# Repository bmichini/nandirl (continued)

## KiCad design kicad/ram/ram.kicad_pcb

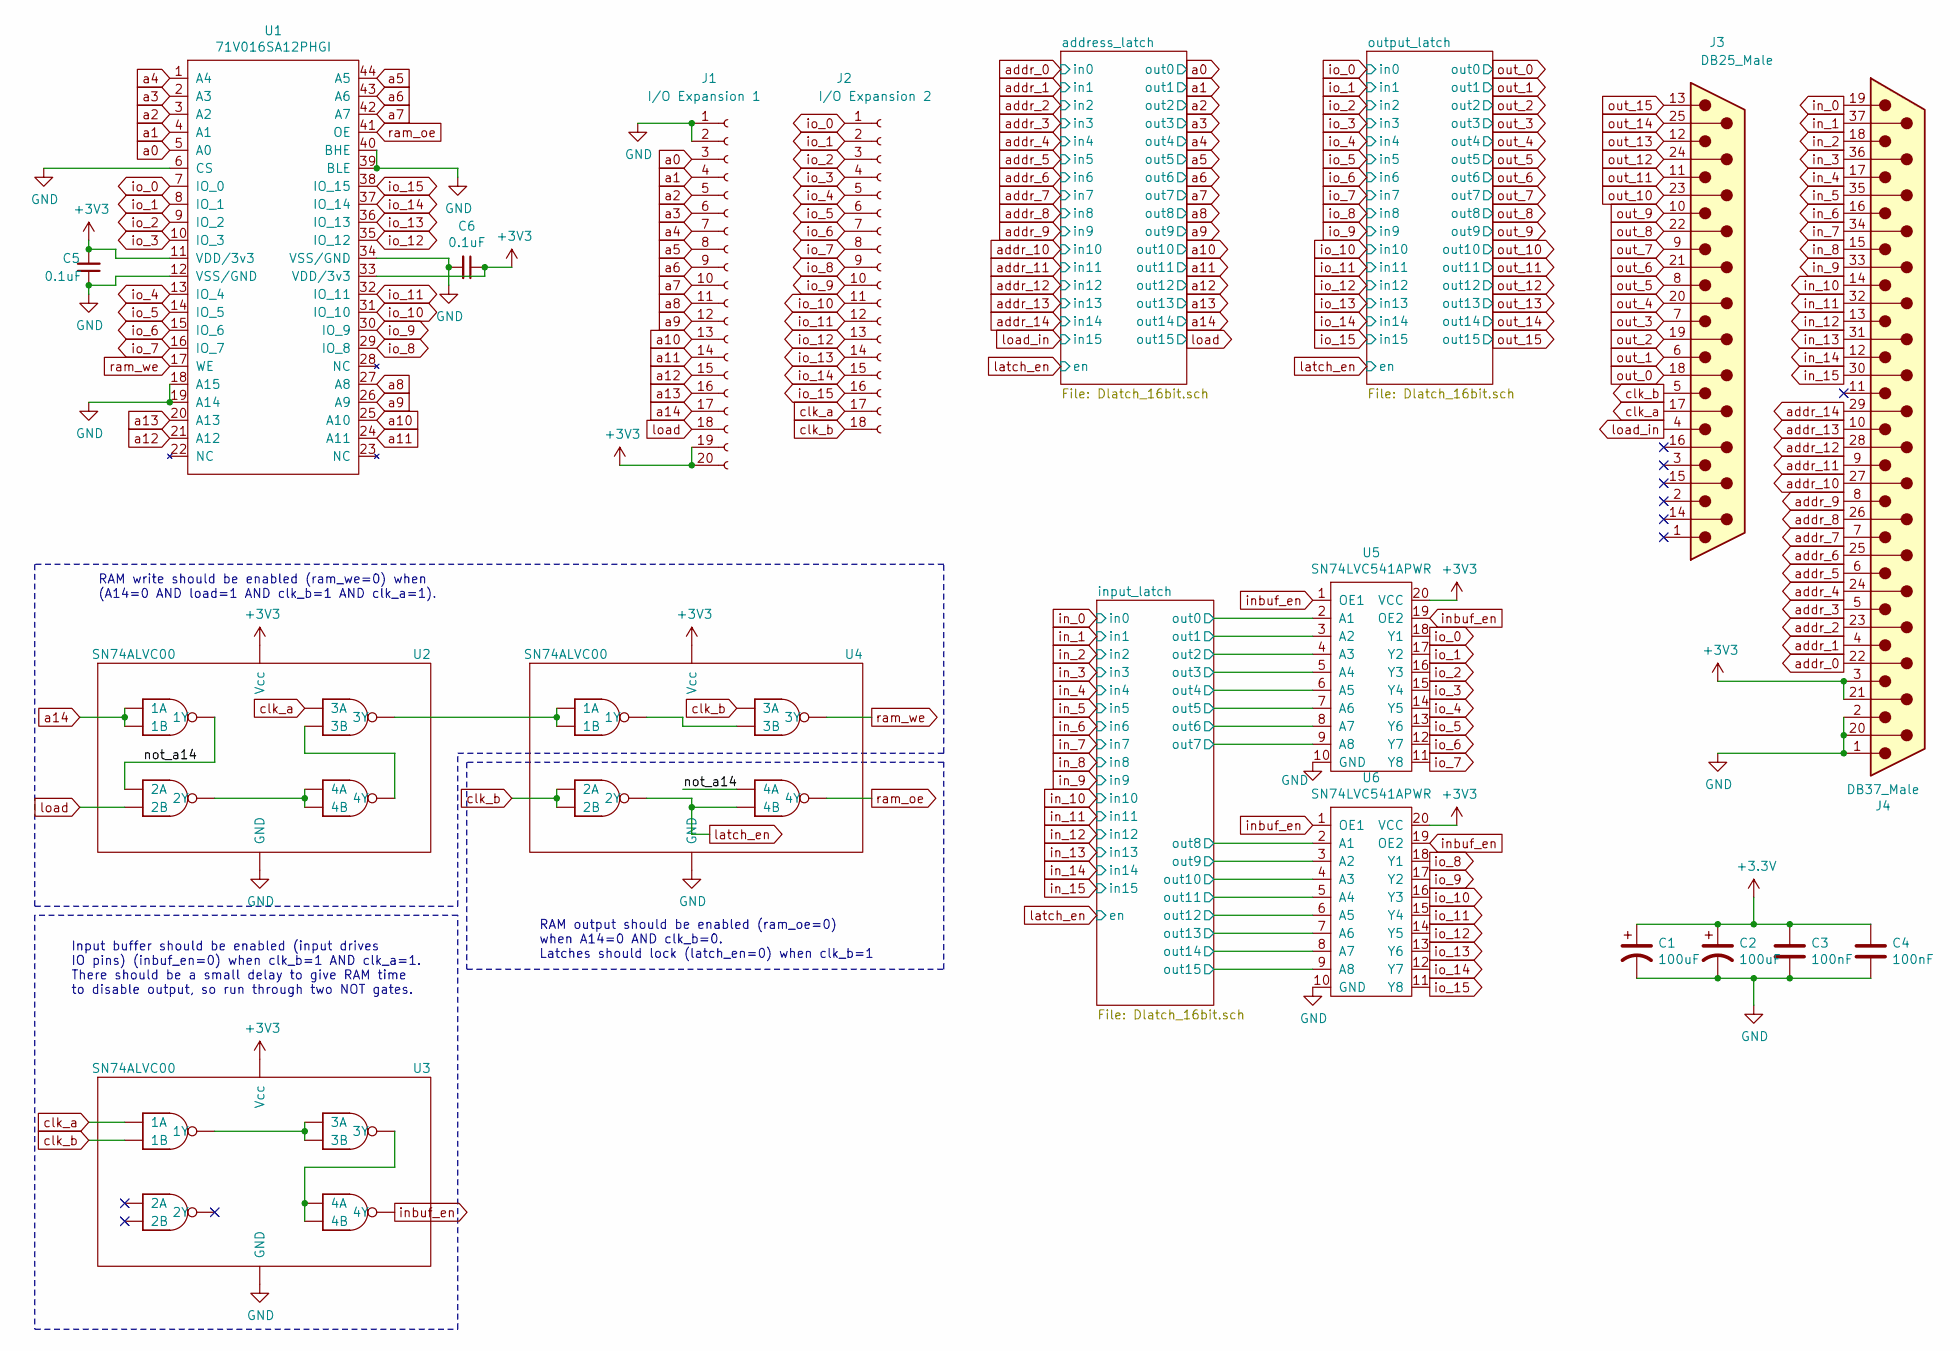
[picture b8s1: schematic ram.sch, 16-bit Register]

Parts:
C1, C2: 100uF; CP_Radial_D8.0mm_P2.50mm; Digikey PN P15797CT-ND
C3, C4: 100nF; C_Disc_D5.0mm_W2.5mm_P5.00mm; Digikey PN BC5229CT-ND
C5, C6: 0.1uF; C_1206_3216Metric; Digikey PN 399-C1206C104K5RAC7800CT-ND
J1: I/O Expansion 1; PinHeader_2x10_P2.54mm_Vertical
J2: I/O Expansion 2; PinHeader_2x09_P2.54mm_Vertical
J3: DB25_Male; DSUB-25_Male_Horizontal_P2.77x2.84mm_EdgePinOffset7.70mm_Ho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; Digikey PN AE10980-ND
J4: DB37_Male; DSUB-37_Male_Horizontal_P2.77x2.84mm_EdgePinOffset7.70mm_Ho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; Digikey PN AE10986-ND
U1: 71V016SA12PHGI; TSOP-II-44_10.16x18.41mm_P0.8mm; Digikey PN 800-2609-5-ND
U2, U3, U4: SN74ALVC00; TSSOP-14_4.4x5mm_P0.65mm; Digikey PN 296-5104-1-ND
U5, U6: SN74LVC541APWR; TSSOP-20_4.4x6.5mm_P0.65mm; Digikey PN 296-8521-1-ND

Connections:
/input_latch/out0: U5.2 (A1); also elsewhere on the board
/input_latch/out1: U5.3 (A2); also elsewhere on the board
/input_latch/out2: U5.4 (A3); also elsewhere on the board
/input_latch/out3: U5.5 (A4); also elsewhere on the board
/input_latch/out4: U5.6 (A5); also elsewhere on the board
/input_latch/out5: U5.7 (A6); also elsewhere on the board
/input_latch/out6: U5.8 (A7); also elsewhere on the board
/input_latch/out7: U5.9 (A8); also elsewhere on the board
/input_latch/out8: U6.2 (A1); also elsewhere on the board
/input_latch/out9: U6.3 (A2); also elsewhere on the board
/input_latch/out10: U6.4 (A3); also elsewhere on the board
/input_latch/out11: U6.5 (A4); also elsewhere on the board
/input_latch/out12: U6.6 (A5); also elsewhere on the board
/input_latch/out13: U6.7 (A6); also elsewhere on the board
/input_latch/out14: U6.8 (A7); also elsewhere on the board
/input_latch/out15: U6.9 (A8); also elsewhere on the board
/not_a14: U2.3 (1Y), U2.4 (2A), U4.12 (4A)
GND: C1.2, C2.2, C3.2, C4.2, C5.1, C6.2, J1.1, J1.2, J4.1, J4.2, J4.20, U1.6 (CS), U1.12 (VSS/GND), U1.18 (A15), U1.19 (A14), U1.34 (VSS/GND), U1.39 (BLE), U1.40 (BHE), U2.7 (GND), U3.7 (GND), U4.7 (GND), U5.10 (GND), U6.10 (GND); also elsewhere on the board
unnamed: U2.8 (3Y), U4.1 (1A), U4.2 (1B)
unnamed: U2.10 (3B), U2.11 (4Y)
unnamed: U2.6 (2Y), U2.12 (4A), U2.13 (4B)
unnamed: U3.3 (1Y), U3.9 (3A), U3.10 (3B)
unnamed: U3.8 (3Y), U3.12 (4A), U3.13 (4B)
unnamed: U4.3 (1Y), U4.10 (3B)
a0: J1.3, U1.5 (A0); also elsewhere on the board
a1: J1.4, U1.4 (A1); also elsewhere on the board
a2: J1.5, U1.3 (A2); also elsewhere on the board
a3: J1.6, U1.2 (A3); also elsewhere on the board
a4: J1.7, U1.1 (A4); also elsewhere on the board
a5: J1.8, U1.44 (A5); also elsewhere on the board
a6: J1.9, U1.43 (A6); also elsewhere on the board
a7: J1.10, U1.42 (A7); also elsewhere on the board
a8: J1.11, U1.27 (A8); also elsewhere on the board
a9: J1.12, U1.26 (A9); also elsewhere on the board
a10: J1.13, U1.25 (A10); also elsewhere on the board
a11: J1.14, U1.24 (A11); also elsewhere on the board
a12: J1.15, U1.21 (A12); also elsewhere on the board
a13: J1.16, U1.20 (A13); also elsewhere on the board
a14: J1.17, U2.1 (1A), U2.2 (1B); also elsewhere on the board
addr_0: J4.22; also elsewhere on the board
addr_1: J4.4; also elsewhere on the board
addr_2: J4.23; also elsewhere on the board
addr_3: J4.5; also elsewhere on the board
addr_4: J4.24; also elsewhere on the board
addr_5: J4.6; also elsewhere on the board
addr_6: J4.25; also elsewhere on the board
addr_7: J4.7; also elsewhere on the board
addr_8: J4.26; also elsewhere on the board
addr_9: J4.8; also elsewhere on the board
addr_10: J4.27; also elsewhere on the board
addr_11: J4.9; also elsewhere on the board
addr_12: J4.28; also elsewhere on the board
addr_13: J4.10; also elsewhere on the board
addr_14: J4.29; also elsewhere on the board
clk_a: J2.17, J3.17, U2.9 (3A), U3.1 (1A)
clk_b: J2.18, J3.5, U3.2 (1B), U4.4 (2A), U4.5 (2B), U4.9 (3A)
in_0: J4.19; also elsewhere on the board
in_1: J4.37; also elsewhere on the board
in_2: J4.18; also elsewhere on the board
in_3: J4.36; also elsewhere on the board
in_4: J4.17; also elsewhere on the board
in_5: J4.35; also elsewhere on the board
in_6: J4.16; also elsewhere on the board
in_7: J4.34; also elsewhere on the board
in_8: J4.15; also elsewhere on the board
in_9: J4.33; also elsewhere on the board
in_10: J4.14; also elsewhere on the board
in_11: J4.32; also elsewhere on the board
in_12: J4.13; also elsewhere on the board
in_13: J4.31; also elsewhere on the board
in_14: J4.12; also elsewhere on the board
in_15: J4.30; also elsewhere on the board
inbuf_en: U3.11 (4Y), U5.1 (OE1), U5.19 (OE2), U6.1 (OE1), U6.19 (OE2)
io_0: J2.1, U1.7 (IO_0), U5.18 (Y1); also elsewhere on the board
io_1: J2.2, U1.8 (IO_1), U5.17 (Y2); also elsewhere on the board
io_2: J2.3, U1.9 (IO_2), U5.16 (Y3); also elsewhere on the board
io_3: J2.4, U1.10 (IO_3), U5.15 (Y4); also elsewhere on the board
io_4: J2.5, U1.13 (IO_4), U5.14 (Y5); also elsewhere on the board
io_5: J2.6, U1.14 (IO_5), U5.13 (Y6); also elsewhere on the board
io_6: J2.7, U1.15 (IO_6), U5.12 (Y7); also elsewhere on the board
io_7: J2.8, U1.16 (IO_7), U5.11 (Y8); also elsewhere on the board
io_8: J2.9, U1.29 (IO_8), U6.18 (Y1); also elsewhere on the board
io_9: J2.10, U1.30 (IO_9), U6.17 (Y2); also elsewhere on the board
io_10: J2.11, U1.31 (IO_10), U6.16 (Y3); also elsewhere on the board
io_11: J2.12, U1.32 (IO_11), U6.15 (Y4); also elsewhere on the board
io_12: J2.13, U1.35 (IO_12), U6.14 (Y5); also elsewhere on the board
io_13: J2.14, U1.36 (IO_13), U6.13 (Y6); also elsewhere on the board
io_14: J2.15, U1.37 (IO_14), U6.12 (Y7); also elsewhere on the board
io_15: J2.16, U1.38 (IO_15), U6.11 (Y8); also elsewhere on the board
latch_en: U4.6 (2Y), U4.13 (4B); also elsewhere on the board
load: J1.18, U2.5 (2B); also elsewhere on the board
load_in: J3.4; also elsewhere on the board
out_0: J3.18; also elsewhere on the board
out_1: J3.6; also elsewhere on the board
out_2: J3.19; also elsewhere on the board
out_3: J3.7; also elsewhere on the board
out_4: J3.20; also elsewhere on the board
out_5: J3.8; also elsewhere on the board
out_6: J3.21; also elsewhere on the board
out_7: J3.9; also elsewhere on the board
out_8: J3.22; also elsewhere on the board
out_9: J3.10; also elsewhere on the board
out_10: J3.23; also elsewhere on the board
out_11: J3.11; also elsewhere on the board
out_12: J3.24; also elsewhere on the board
out_13: J3.12; also elsewhere on the board
out_14: J3.25; also elsewhere on the board
out_15: J3.13; also elsewhere on the board
ram_oe: U1.41 (OE), U4.11 (4Y)
ram_we: U1.17 (WE), U4.8 (3Y)

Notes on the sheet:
Input buffer should be enabled (input drives IO pins) (inbuf_en=0) when clk_b=1 AND clk_a=1. There should be a small delay to give RAM time to disable output, so run through two NOT gates.
RAM write should be enabled (ram_we=0) when (A14=0 AND load=1 AND clk_b=1 AND clk_a=1).
RAM output should be enabled (ram_oe=0) when A14=0 AND clk_b=0. Latches should lock (latch_en=0) when clk_b=1

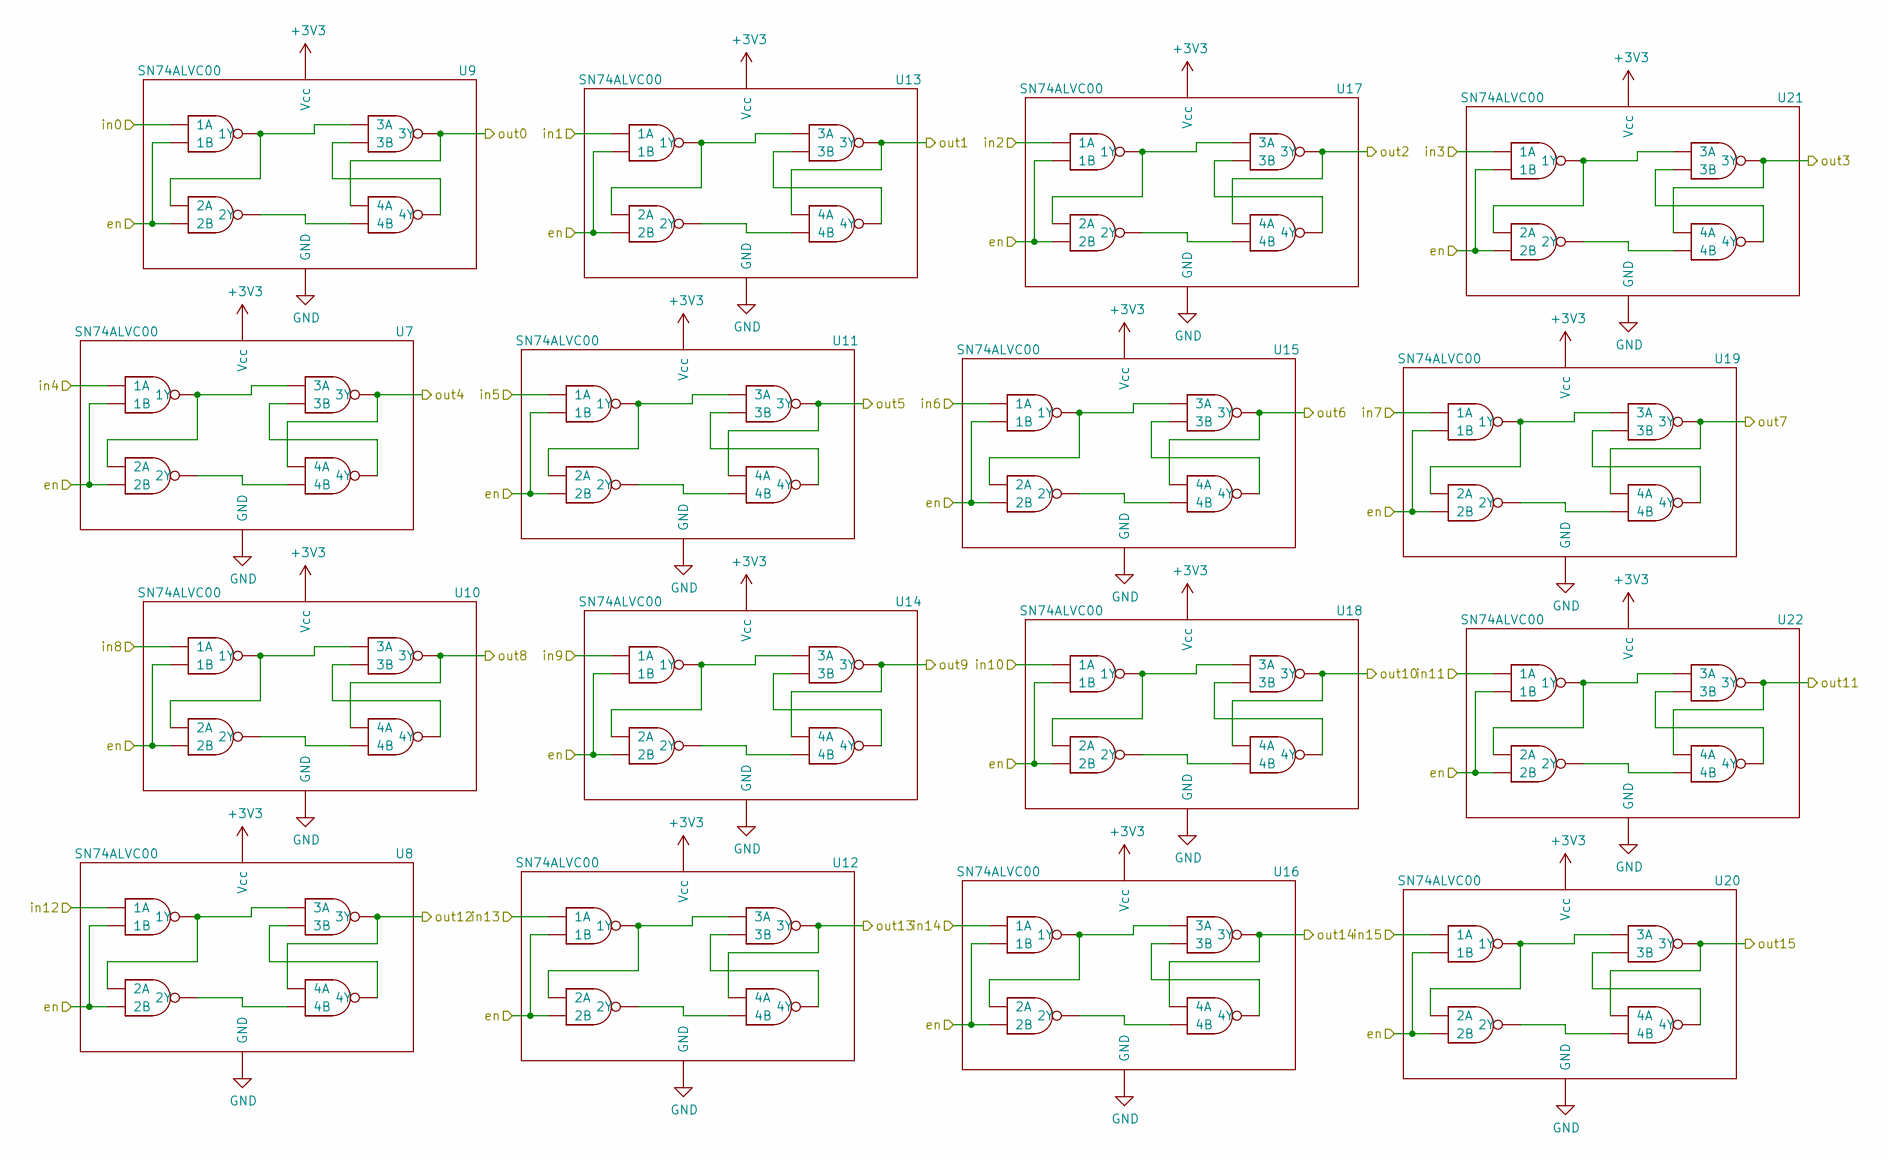
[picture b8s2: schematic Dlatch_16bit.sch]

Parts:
U39, U40, U41, U42, U43, U44, U45, U46, U47, U48, U49, U50, U51, U52, U53, U54: SN74ALVC00; TSSOP-14_4.4x5mm_P0.65mm; Digikey PN 296-5104-1-ND

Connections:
/input_latch/out0: U41.8 (3Y), U41.12 (4A); also elsewhere on the board
/input_latch/out1: U45.8 (3Y), U45.12 (4A); also elsewhere on the board
/input_latch/out2: U49.8 (3Y), U49.12 (4A); also elsewhere on the board
/input_latch/out3: U53.8 (3Y), U53.12 (4A); also elsewhere on the board
/input_latch/out4: U39.8 (3Y), U39.12 (4A); also elsewhere on the board
/input_latch/out5: U43.8 (3Y), U43.12 (4A); also elsewhere on the board
/input_latch/out6: U47.8 (3Y), U47.12 (4A); also elsewhere on the board
/input_latch/out7: U51.8 (3Y), U51.12 (4A); also elsewhere on the board
/input_latch/out8: U42.8 (3Y), U42.12 (4A); also elsewhere on the board
/input_latch/out9: U46.8 (3Y), U46.12 (4A); also elsewhere on the board
/input_latch/out10: U50.8 (3Y), U50.12 (4A); also elsewhere on the board
/input_latch/out11: U54.8 (3Y), U54.12 (4A); also elsewhere on the board
/input_latch/out12: U40.8 (3Y), U40.12 (4A); also elsewhere on the board
/input_latch/out13: U44.8 (3Y), U44.12 (4A); also elsewhere on the board
/input_latch/out14: U48.8 (3Y), U48.12 (4A); also elsewhere on the board
/input_latch/out15: U52.8 (3Y), U52.12 (4A); also elsewhere on the board
GND: U39.7 (GND), U40.7 (GND), U41.7 (GND), U42.7 (GND), U43.7 (GND), U44.7 (GND), U45.7 (GND), U46.7 (GND), U47.7 (GND), U48.7 (GND), U49.7 (GND), U50.7 (GND), U51.7 (GND), U52.7 (GND), U53.7 (GND), U54.7 (GND); also elsewhere on the board
unnamed: U39.3 (1Y), U39.4 (2A), U39.9 (3A)
unnamed: U39.10 (3B), U39.11 (4Y)
unnamed: U39.6 (2Y), U39.13 (4B)
unnamed: U40.3 (1Y), U40.4 (2A), U40.9 (3A)
unnamed: U40.10 (3B), U40.11 (4Y)
unnamed: U40.6 (2Y), U40.13 (4B)
unnamed: U41.3 (1Y), U41.4 (2A), U41.9 (3A)
unnamed: U41.10 (3B), U41.11 (4Y)
unnamed: U41.6 (2Y), U41.13 (4B)
unnamed: U42.3 (1Y), U42.4 (2A), U42.9 (3A)
unnamed: U42.10 (3B), U42.11 (4Y)
unnamed: U42.6 (2Y), U42.13 (4B)
unnamed: U43.3 (1Y), U43.4 (2A), U43.9 (3A)
unnamed: U43.10 (3B), U43.11 (4Y)
unnamed: U43.6 (2Y), U43.13 (4B)
unnamed: U44.3 (1Y), U44.4 (2A), U44.9 (3A)
unnamed: U44.10 (3B), U44.11 (4Y)
unnamed: U44.6 (2Y), U44.13 (4B)
unnamed: U45.3 (1Y), U45.4 (2A), U45.9 (3A)
unnamed: U45.10 (3B), U45.11 (4Y)
unnamed: U45.6 (2Y), U45.13 (4B)
unnamed: U46.3 (1Y), U46.4 (2A), U46.9 (3A)
unnamed: U46.10 (3B), U46.11 (4Y)
unnamed: U46.6 (2Y), U46.13 (4B)
unnamed: U47.3 (1Y), U47.4 (2A), U47.9 (3A)
unnamed: U47.10 (3B), U47.11 (4Y)
unnamed: U47.6 (2Y), U47.13 (4B)
unnamed: U48.3 (1Y), U48.4 (2A), U48.9 (3A)
unnamed: U48.10 (3B), U48.11 (4Y)
unnamed: U48.6 (2Y), U48.13 (4B)
unnamed: U49.3 (1Y), U49.4 (2A), U49.9 (3A)
unnamed: U49.10 (3B), U49.11 (4Y)
unnamed: U49.6 (2Y), U49.13 (4B)
unnamed: U50.3 (1Y), U50.4 (2A), U50.9 (3A)
unnamed: U50.10 (3B), U50.11 (4Y)
unnamed: U50.6 (2Y), U50.13 (4B)
unnamed: U51.3 (1Y), U51.4 (2A), U51.9 (3A)
unnamed: U51.10 (3B), U51.11 (4Y)
unnamed: U51.6 (2Y), U51.13 (4B)
unnamed: U52.3 (1Y), U52.4 (2A), U52.9 (3A)
unnamed: U52.10 (3B), U52.11 (4Y)
unnamed: U52.6 (2Y), U52.13 (4B)
unnamed: U53.3 (1Y), U53.4 (2A), U53.9 (3A)
unnamed: U53.10 (3B), U53.11 (4Y)
unnamed: U53.6 (2Y), U53.13 (4B)
unnamed: U54.3 (1Y), U54.4 (2A), U54.9 (3A)
unnamed: U54.10 (3B), U54.11 (4Y)
unnamed: U54.6 (2Y), U54.13 (4B)
in_0: U41.1 (1A); also elsewhere on the board
in_1: U45.1 (1A); also elsewhere on the board
in_2: U49.1 (1A); also elsewhere on the board
in_3: U53.1 (1A); also elsewhere on the board
in_4: U39.1 (1A); also elsewhere on the board
in_5: U43.1 (1A); also elsewhere on the board
in_6: U47.1 (1A); also elsewhere on the board
in_7: U51.1 (1A); also elsewhere on the board
in_8: U42.1 (1A); also elsewhere on the board
in_9: U46.1 (1A); also elsewhere on the board
in_10: U50.1 (1A); also elsewhere on the board
in_11: U54.1 (1A); also elsewhere on the board
in_12: U40.1 (1A); also elsewhere on the board
in_13: U44.1 (1A); also elsewhere on the board
in_14: U48.1 (1A); also elsewhere on the board
in_15: U52.1 (1A); also elsewhere on the board
latch_en: U39.2 (1B), U39.5 (2B), U40.2 (1B), U40.5 (2B), U41.2 (1B), U41.5 (2B), U42.2 (1B), U42.5 (2B), U43.2 (1B), U43.5 (2B), U44.2 (1B), U44.5 (2B), U45.2 (1B), U45.5 (2B), U46.2 (1B), U46.5 (2B), U47.2 (1B), U47.5 (2B), U48.2 (1B), U48.5 (2B), U49.2 (1B), U49.5 (2B), U50.2 (1B), U50.5 (2B), U51.2 (1B), U51.5 (2B), U52.2 (1B), U52.5 (2B), U53.2 (1B), U53.5 (2B), U54.2 (1B), U54.5 (2B); also elsewhere on the board

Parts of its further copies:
U7, U8, U9, U10, U11, U12, U13, U14, U15, U16, U17, U18, U19, U20, U21, U22, U23, U24, U25, U26, U27, U28, U29, U30, U31, U32, U33, U34, U35, U36, U37, U38: SN74ALVC00; TSSOP-14_4.4x5mm_P0.65mm; Digikey PN 296-5104-1-ND

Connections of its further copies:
GND: U7.7 (GND), U8.7 (GND), U9.7 (GND), U10.7 (GND), U11.7 (GND), U12.7 (GND), U13.7 (GND), U14.7 (GND), U15.7 (GND), U16.7 (GND), U17.7 (GND), U18.7 (GND), U19.7 (GND), U20.7 (GND), U21.7 (GND), U22.7 (GND), U23.7 (GND), U24.7 (GND), U25.7 (GND), U26.7 (GND), U27.7 (GND), U28.7 (GND), U29.7 (GND), U30.7 (GND), U31.7 (GND), U32.7 (GND), U33.7 (GND), U34.7 (GND), U35.7 (GND), U36.7 (GND), U37.7 (GND), U38.7 (GND); also elsewhere on the board
unnamed: U7.3 (1Y), U7.4 (2A), U7.9 (3A)
unnamed: U7.10 (3B), U7.11 (4Y)
unnamed: U7.6 (2Y), U7.13 (4B)
unnamed: U8.3 (1Y), U8.4 (2A), U8.9 (3A)
unnamed: U8.10 (3B), U8.11 (4Y)
unnamed: U8.6 (2Y), U8.13 (4B)
unnamed: U9.3 (1Y), U9.4 (2A), U9.9 (3A)
unnamed: U9.10 (3B), U9.11 (4Y)
unnamed: U9.6 (2Y), U9.13 (4B)
unnamed: U10.3 (1Y), U10.4 (2A), U10.9 (3A)
unnamed: U10.10 (3B), U10.11 (4Y)
unnamed: U10.6 (2Y), U10.13 (4B)
unnamed: U11.3 (1Y), U11.4 (2A), U11.9 (3A)
unnamed: U11.10 (3B), U11.11 (4Y)
unnamed: U11.6 (2Y), U11.13 (4B)
unnamed: U12.3 (1Y), U12.4 (2A), U12.9 (3A)
unnamed: U12.10 (3B), U12.11 (4Y)
unnamed: U12.6 (2Y), U12.13 (4B)
unnamed: U13.3 (1Y), U13.4 (2A), U13.9 (3A)
unnamed: U13.10 (3B), U13.11 (4Y)
unnamed: U13.6 (2Y), U13.13 (4B)
unnamed: U14.3 (1Y), U14.4 (2A), U14.9 (3A)
unnamed: U14.10 (3B), U14.11 (4Y)
unnamed: U14.6 (2Y), U14.13 (4B)
unnamed: U15.3 (1Y), U15.4 (2A), U15.9 (3A)
unnamed: U15.10 (3B), U15.11 (4Y)
unnamed: U15.6 (2Y), U15.13 (4B)
unnamed: U16.3 (1Y), U16.4 (2A), U16.9 (3A)
unnamed: U16.10 (3B), U16.11 (4Y)
unnamed: U16.6 (2Y), U16.13 (4B)
unnamed: U17.3 (1Y), U17.4 (2A), U17.9 (3A)
unnamed: U17.10 (3B), U17.11 (4Y)
unnamed: U17.6 (2Y), U17.13 (4B)
unnamed: U18.3 (1Y), U18.4 (2A), U18.9 (3A)
unnamed: U18.10 (3B), U18.11 (4Y)
unnamed: U18.6 (2Y), U18.13 (4B)
unnamed: U19.3 (1Y), U19.4 (2A), U19.9 (3A)
unnamed: U19.10 (3B), U19.11 (4Y)
unnamed: U19.6 (2Y), U19.13 (4B)
unnamed: U20.3 (1Y), U20.4 (2A), U20.9 (3A)
unnamed: U20.10 (3B), U20.11 (4Y)
unnamed: U20.6 (2Y), U20.13 (4B)
unnamed: U21.3 (1Y), U21.4 (2A), U21.9 (3A)
unnamed: U21.10 (3B), U21.11 (4Y)
unnamed: U21.6 (2Y), U21.13 (4B)
unnamed: U22.3 (1Y), U22.4 (2A), U22.9 (3A)
unnamed: U22.10 (3B), U22.11 (4Y)
unnamed: U22.6 (2Y), U22.13 (4B)
unnamed: U23.3 (1Y), U23.4 (2A), U23.9 (3A)
unnamed: U23.10 (3B), U23.11 (4Y)
unnamed: U23.6 (2Y), U23.13 (4B)
unnamed: U24.3 (1Y), U24.4 (2A), U24.9 (3A)
unnamed: U24.10 (3B), U24.11 (4Y)
unnamed: U24.6 (2Y), U24.13 (4B)
unnamed: U25.3 (1Y), U25.4 (2A), U25.9 (3A)
unnamed: U25.10 (3B), U25.11 (4Y)
unnamed: U25.6 (2Y), U25.13 (4B)
unnamed: U26.3 (1Y), U26.4 (2A), U26.9 (3A)
unnamed: U26.10 (3B), U26.11 (4Y)
unnamed: U26.6 (2Y), U26.13 (4B)
unnamed: U27.3 (1Y), U27.4 (2A), U27.9 (3A)
unnamed: U27.10 (3B), U27.11 (4Y)
unnamed: U27.6 (2Y), U27.13 (4B)
unnamed: U28.3 (1Y), U28.4 (2A), U28.9 (3A)
unnamed: U28.10 (3B), U28.11 (4Y)
unnamed: U28.6 (2Y), U28.13 (4B)
unnamed: U29.3 (1Y), U29.4 (2A), U29.9 (3A)
unnamed: U29.10 (3B), U29.11 (4Y)
unnamed: U29.6 (2Y), U29.13 (4B)
unnamed: U30.3 (1Y), U30.4 (2A), U30.9 (3A)
unnamed: U30.10 (3B), U30.11 (4Y)
unnamed: U30.6 (2Y), U30.13 (4B)
unnamed: U31.3 (1Y), U31.4 (2A), U31.9 (3A)
unnamed: U31.10 (3B), U31.11 (4Y)
unnamed: U31.6 (2Y), U31.13 (4B)
unnamed: U32.3 (1Y), U32.4 (2A), U32.9 (3A)
unnamed: U32.10 (3B), U32.11 (4Y)
unnamed: U32.6 (2Y), U32.13 (4B)
unnamed: U33.3 (1Y), U33.4 (2A), U33.9 (3A)
unnamed: U33.10 (3B), U33.11 (4Y)
unnamed: U33.6 (2Y), U33.13 (4B)
unnamed: U34.3 (1Y), U34.4 (2A), U34.9 (3A)
unnamed: U34.10 (3B), U34.11 (4Y)
unnamed: U34.6 (2Y), U34.13 (4B)
unnamed: U35.3 (1Y), U35.4 (2A), U35.9 (3A)
unnamed: U35.10 (3B), U35.11 (4Y)
unnamed: U35.6 (2Y), U35.13 (4B)
unnamed: U36.3 (1Y), U36.4 (2A), U36.9 (3A)
unnamed: U36.10 (3B), U36.11 (4Y)
unnamed: U36.6 (2Y), U36.13 (4B)
unnamed: U37.3 (1Y), U37.4 (2A), U37.9 (3A)
unnamed: U37.10 (3B), U37.11 (4Y)
unnamed: U37.6 (2Y), U37.13 (4B)
unnamed: U38.3 (1Y), U38.4 (2A), U38.9 (3A)
unnamed: U38.10 (3B), U38.11 (4Y)
unnamed: U38.6 (2Y), U38.13 (4B)
a0: U25.8 (3Y), U25.12 (4A); also elsewhere on the board
a1: U29.8 (3Y), U29.12 (4A); also elsewhere on the board
a2: U33.8 (3Y), U33.12 (4A); also elsewhere on the board
a3: U37.8 (3Y), U37.12 (4A); also elsewhere on the board
a4: U23.8 (3Y), U23.12 (4A); also elsewhere on the board
a5: U27.8 (3Y), U27.12 (4A); also elsewhere on the board
a6: U31.8 (3Y), U31.12 (4A); also elsewhere on the board
a7: U35.8 (3Y), U35.12 (4A); also elsewhere on the board
a8: U26.8 (3Y), U26.12 (4A); also elsewhere on the board
a9: U30.8 (3Y), U30.12 (4A); also elsewhere on the board
a10: U34.8 (3Y), U34.12 (4A); also elsewhere on the board
a11: U38.8 (3Y), U38.12 (4A); also elsewhere on the board
a12: U24.8 (3Y), U24.12 (4A); also elsewhere on the board
a13: U28.8 (3Y), U28.12 (4A); also elsewhere on the board
a14: U32.8 (3Y), U32.12 (4A); also elsewhere on the board
addr_0: U25.1 (1A); also elsewhere on the board
addr_1: U29.1 (1A); also elsewhere on the board
addr_2: U33.1 (1A); also elsewhere on the board
addr_3: U37.1 (1A); also elsewhere on the board
addr_4: U23.1 (1A); also elsewhere on the board
addr_5: U27.1 (1A); also elsewhere on the board
addr_6: U31.1 (1A); also elsewhere on the board
addr_7: U35.1 (1A); also elsewhere on the board
addr_8: U26.1 (1A); also elsewhere on the board
addr_9: U30.1 (1A); also elsewhere on the board
addr_10: U34.1 (1A); also elsewhere on the board
addr_11: U38.1 (1A); also elsewhere on the board
addr_12: U24.1 (1A); also elsewhere on the board
addr_13: U28.1 (1A); also elsewhere on the board
addr_14: U32.1 (1A); also elsewhere on the board
io_0: U9.1 (1A); also elsewhere on the board
io_1: U13.1 (1A); also elsewhere on the board
io_2: U17.1 (1A); also elsewhere on the board
io_3: U21.1 (1A); also elsewhere on the board
io_4: U7.1 (1A); also elsewhere on the board
io_5: U11.1 (1A); also elsewhere on the board
io_6: U15.1 (1A); also elsewhere on the board
io_7: U19.1 (1A); also elsewhere on the board
io_8: U10.1 (1A); also elsewhere on the board
io_9: U14.1 (1A); also elsewhere on the board
io_10: U18.1 (1A); also elsewhere on the board
io_11: U22.1 (1A); also elsewhere on the board
io_12: U8.1 (1A); also elsewhere on the board
io_13: U12.1 (1A); also elsewhere on the board
io_14: U16.1 (1A); also elsewhere on the board
io_15: U20.1 (1A); also elsewhere on the board
latch_en: U7.2 (1B), U7.5 (2B), U8.2 (1B), U8.5 (2B), U9.2 (1B), U9.5 (2B), U10.2 (1B), U10.5 (2B), U11.2 (1B), U11.5 (2B), U12.2 (1B), U12.5 (2B), U13.2 (1B), U13.5 (2B), U14.2 (1B), U14.5 (2B), U15.2 (1B), U15.5 (2B), U16.2 (1B), U16.5 (2B), U17.2 (1B), U17.5 (2B), U18.2 (1B), U18.5 (2B), U19.2 (1B), U19.5 (2B), U20.2 (1B), U20.5 (2B), U21.2 (1B), U21.5 (2B), U22.2 (1B), U22.5 (2B), U23.2 (1B), U23.5 (2B), U24.2 (1B), U24.5 (2B), U25.2 (1B), U25.5 (2B), U26.2 (1B), U26.5 (2B), U27.2 (1B), U27.5 (2B), U28.2 (1B), U28.5 (2B), U29.2 (1B), U29.5 (2B), U30.2 (1B), U30.5 (2B), U31.2 (1B), U31.5 (2B), U32.2 (1B), U32.5 (2B), U33.2 (1B), U33.5 (2B), U34.2 (1B), U34.5 (2B), U35.2 (1B), U35.5 (2B), U36.2 (1B), U36.5 (2B), U37.2 (1B), U37.5 (2B), U38.2 (1B), U38.5 (2B); also elsewhere on the board
load: U36.8 (3Y), U36.12 (4A); also elsewhere on the board
load_in: U36.1 (1A); also elsewhere on the board
out_0: U9.8 (3Y), U9.12 (4A); also elsewhere on the board
out_1: U13.8 (3Y), U13.12 (4A); also elsewhere on the board
out_2: U17.8 (3Y), U17.12 (4A); also elsewhere on the board
out_3: U21.8 (3Y), U21.12 (4A); also elsewhere on the board
out_4: U7.8 (3Y), U7.12 (4A); also elsewhere on the board
out_5: U11.8 (3Y), U11.12 (4A); also elsewhere on the board
out_6: U15.8 (3Y), U15.12 (4A); also elsewhere on the board
out_7: U19.8 (3Y), U19.12 (4A); also elsewhere on the board
out_8: U10.8 (3Y), U10.12 (4A); also elsewhere on the board
out_9: U14.8 (3Y), U14.12 (4A); also elsewhere on the board
out_10: U18.8 (3Y), U18.12 (4A); also elsewhere on the board
out_11: U22.8 (3Y), U22.12 (4A); also elsewhere on the board
out_12: U8.8 (3Y), U8.12 (4A); also elsewhere on the board
out_13: U12.8 (3Y), U12.12 (4A); also elsewhere on the board
out_14: U16.8 (3Y), U16.12 (4A); also elsewhere on the board
out_15: U20.8 (3Y), U20.12 (4A); also elsewhere on the board

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
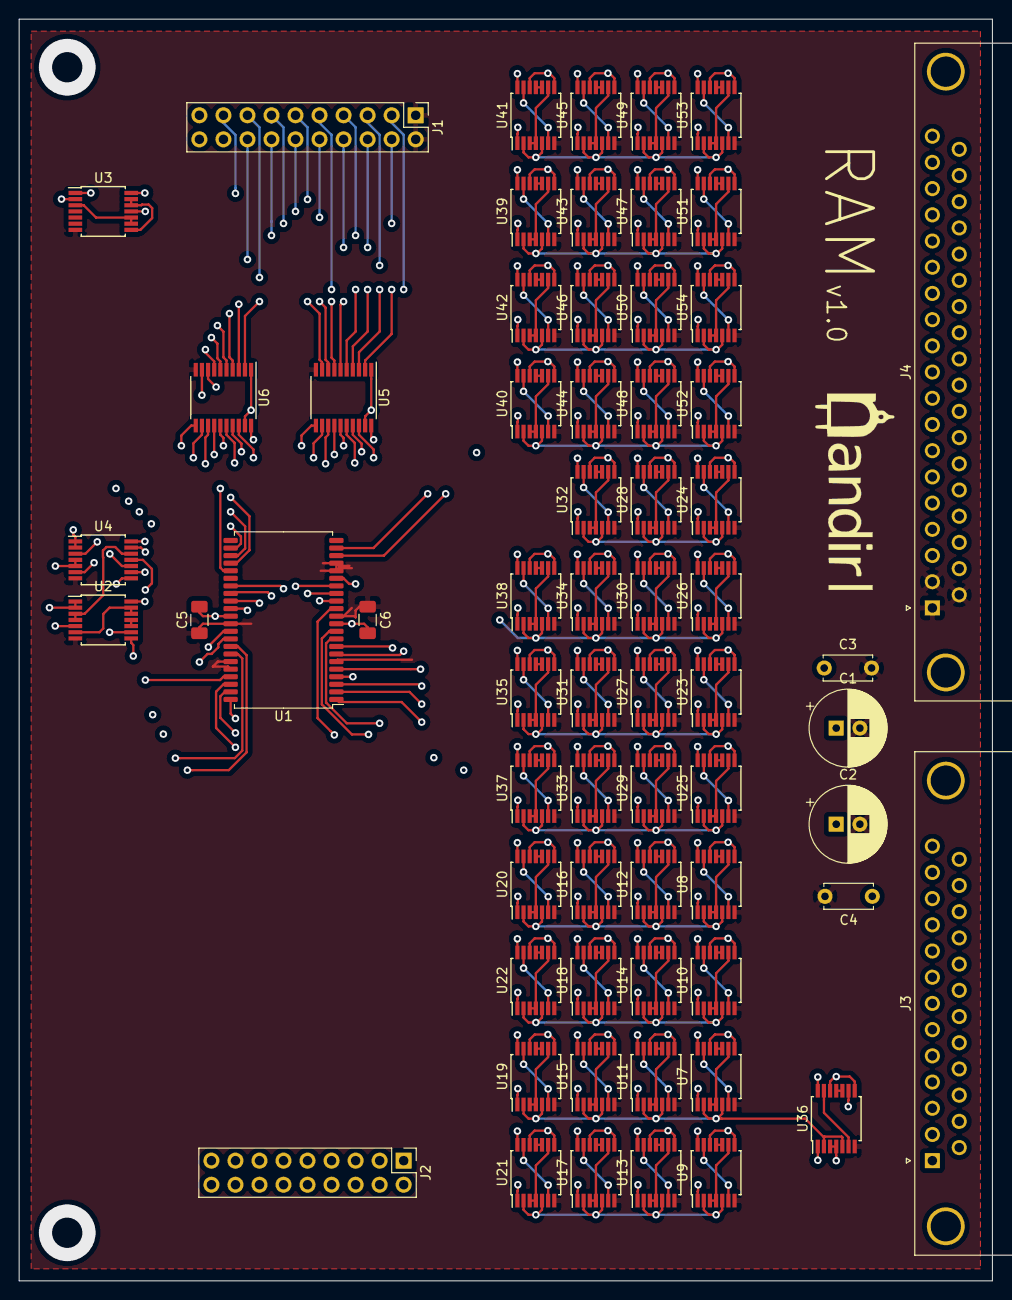
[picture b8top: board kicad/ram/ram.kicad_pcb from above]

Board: 4 copper layers, 102.9 x 133.3 mm, 64 parts (0 on the bottom side), 255 nets.

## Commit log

2020-03-16 Schematic capture of 1-bit register based on DFF and SRFF. Initial creation of 16-bit register hierarchical schematic.
2020-03-20 Finished initial PCB layout and routing for 16-bit register.
2020-04-01 Added clock generator, tested on breadboard. Added motherboard, routing unfinished. Various component updates.
2020-04-04 Motherboard fully routed, PCB layout done
2020-04-04 Part imports (#1)
    * Schematic capture of 1-bit register based on DFF and SRFF. Initial creation of 16-bit register hierarchical schematic.
    * Finished initial PCB layout and routing for 16-bit register.
    * Added clock generator, tested on breadboard. Added motherboard, routing unfinished. Various component updates.
    * Motherboard fully routed, PCB layout done. README updated.
2020-04-05 Schematic and layout for Program Counter complete.
2020-04-05 Small routing mods
2020-04-05 Fix README
2020-04-05 Program counter (#2)
    * Schematic and layout for Program Counter complete.
    * Small routing mods
    * Fix README
2020-04-05 Updated motherboard with ROM OE,WE, and additional address pins
2020-04-05 ROM schematic, layout, routing complete.
2020-04-07 Rom (#3)
    * Updated motherboard with ROM OE,WE, and additional address pins
    * ROM schematic, layout, routing complete.
2020-04-07 Flipped clk A and clk B based on timing plan.
2020-04-07 Flipped clk A and clk B based on timing plan. (#4)
2020-04-11 Flipped clk A and B based on timing diagram. Added output buffers for clock signals.
2020-04-11 Added clock output enable signal to motherboard debugger. Updated component library.
2020-04-11 Schematic and layout for RAM board complete.
2020-04-15 ALU schematic complete, ready for layout and routing.
2020-04-21 ALU schematic, layout, routing complete. Associated motherboardmod. Also added Load LED to register and program counter boards.
2020-04-21 Ram (#5)
    * Flipped clk A and B based on timing diagram. Added output buffers for clock signals.
    * Added clock output enable signal to motherboard debugger. Updated component library.
    * Schematic and layout for RAM board complete.
    * ALU schematic complete, ready for layout and routing.
    * ALU layout, routing complete. Associated motherboard mod.
    * Added Load LED to register and program counter boards.
2020-04-21 Readme intro section
2020-04-22 Board revisions for manufacturing, add digikey PNs to all, added logo.
2020-04-22 Readme updates (#6)
    * Readme intro section
    * Board revisions for manufacturing, add digikey PNs to all, added logo.
2020-04-23 Created gerbers for first board run.
2020-04-25 Added debugger, schematic and pcb complete.
2020-05-07 lots of updates
2020-06-06 All boards as fabbed at v1.0
2020-06-06 Readme (#7)
    * update
    * Added debugger, schematic and pcb complete.
    * lots of updates
    * All boards as fabbed at v1.0
2020-06-06 Motherboard: Added power switch, moved reset switch, modified silkscreens for readability, fixed A-register connector pinout, grounded NC input pins, changed paste layer clearance to -0.05mm
2020-06-06 Motherboard: Added power switch, moved reset switch, modified silkscreens for readability, fixed A-register connector pinout, grounded NC input pins, changed paste layer clearance to -0.05mm (#8)
2020-06-08 RAM board rework complete. Added COTS latch chips and Teensy 4.1 peripheral + magjack for ethernet.
2020-06-08 Schematic cleanup
2020-06-08 Ram updates (#9)
    * RAM board rework complete. Added COTS latch chips and Teensy 4.1 peripheral + magjack for ethernet.
    * Schematic cleanup
2020-06-08 Debugger updated to Teensy 4.1 with magjack for ethernet. Updated motherboard<>debugger pinout to include 3.3v source
2020-06-08 Added 2 mils extra clearance for paste layer
2020-06-08 cleanup
2020-06-08 Debugger updates (#10)
    * Debugger updated to Teensy 4.1 with magjack for ethernet. Updated motherboard<>debugger pinout to include 3.3v source
    * Added 2 mils extra clearance for paste layer
    * cleanup
2020-06-09 readme updates
2020-06-12 docs index
2020-06-12 docs index (#11)
2020-06-12 Set theme jekyll-theme-slate
2020-06-12 Doc updates
2020-06-12 Readme updates (#12)
    * readme updates
    * Doc updates
2020-06-12 Set theme jekyll-theme-cayman
2026-03-31 WIP checkin
